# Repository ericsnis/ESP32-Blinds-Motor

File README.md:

# ESP32 Blinds Motor
Blind motor automation using MQTT & ESP32

## Features

  It connects to an MQTT server and:
  - checks washing blinds open/closed status (topic blinds/nbrblind1)
    - MQTT subscription can be changed to suit by changing TOPIC1
  - checks current open/closed flag
    - Ignores MQTT command if the flag and the MQTT status are the same
  - opens and closes blinds based on status
  - Polls the open and close blinds and calibration buttons
    - If calibration button is pressed it toggles calibration mode
      - Lights status LED to indicate in calibration mode
      - Open blinds button steps motor toward open 1/4 turn
      - Close blinds button steps motor toward closed 1/4 turn
    - If out of calibration mode
      - Open blinds button rotates motor toward full open
      - Close blinds button rotates motor toward full closed
    - Up & Down also updates the blind status in MQTT
    - Pin definitions
      - Calibration on pin 5
      - Up button on pin 39
      - Down button on pin 36
    Amount of backlash in the blinds rod can be adjusted

  Stepper driver info
  - Uses ULN2003 based board KS0327 Keyestudio stepper motor drive board
  - The stepper driver is attached to digital pins 9, 13, 12 & 14 of the ESP32.
    - Pins defined as Stepper1In1, Stepper1In2, Stepper1In3, etc.
    - Connect in the order they appear on board i.e. In1, In2, In3, In4
  - Driver board should be connected to 5V source

  Assumes use of ESP32 based NodeMCU board, not similarly named ESP8266 NodeMCU.
  - Can be changed to other boards if pinout is changed

  Uses the following libraries
  - Arduino stepper library released under GNU Lesser General Public
  - PubSubClient by Nick O'Leary released under MIT license

## Boards
The schematic folder contains the board and schematic files in Eagle format
- Designs use 1206 SMT LEDs and resistors
- One design excludes headers for endstop microswitches
- One design includes a header for a endstop microswitch

- ESP32 Blinds Motor

- ESP32 Blinds Motor w/ Endstop Header

## Code
The code folder contains the program code to compile and upload to the ESP32
- Use [Platform.io](https://docs.platformio.org/en/latest/integration/ide/vscode.html) installed on [Visual Studio Code](https://code.visualstudio.com/) AKA: VSCode to compile and upload.
- Open the code folder in VSCode then compile, PlatformIO should download any dependencies.
- Project Environments
  - esp32dev-steppermqtt no endstops - Firmware without endstops enabled
  - esp32dev-stepper mqtt with endstop - Firmware with endstops enabled
  - esp32dev-stepper test - Stepper motor connection test

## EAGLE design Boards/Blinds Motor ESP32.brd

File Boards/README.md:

# Boards
 The schematic folder contains the board and schematic files in Eagle format

## Files for ESP32 Blinds Motor w/o Endstop Headers
- _Blinds Motor ESP32.brd_ - Blinds Motor board file
- _Blinds Motor ESP32.sch_ - Blinds Motor schematic file

## Files for ESP32 Blinds Motor with Endstop Headers
- _Blinds Motor ESP32 w endstops.brd_ - Blinds Motor with Endstop board file
- _Blinds Motor ESP32 w endstops.sch_ - Blinds Motor with Endstop schematic file

**You need _both_ the .brd and .sch files to open the board in Eagle.**

## Designs
- One design excludes headers for endstop microswitches
- One design includes a header for a endstop microswitch
ESP32 Blinds Motor

ESP32 Blinds Motor w/ Endstop Header

**Files are provided as is with no guarantees express or implied**

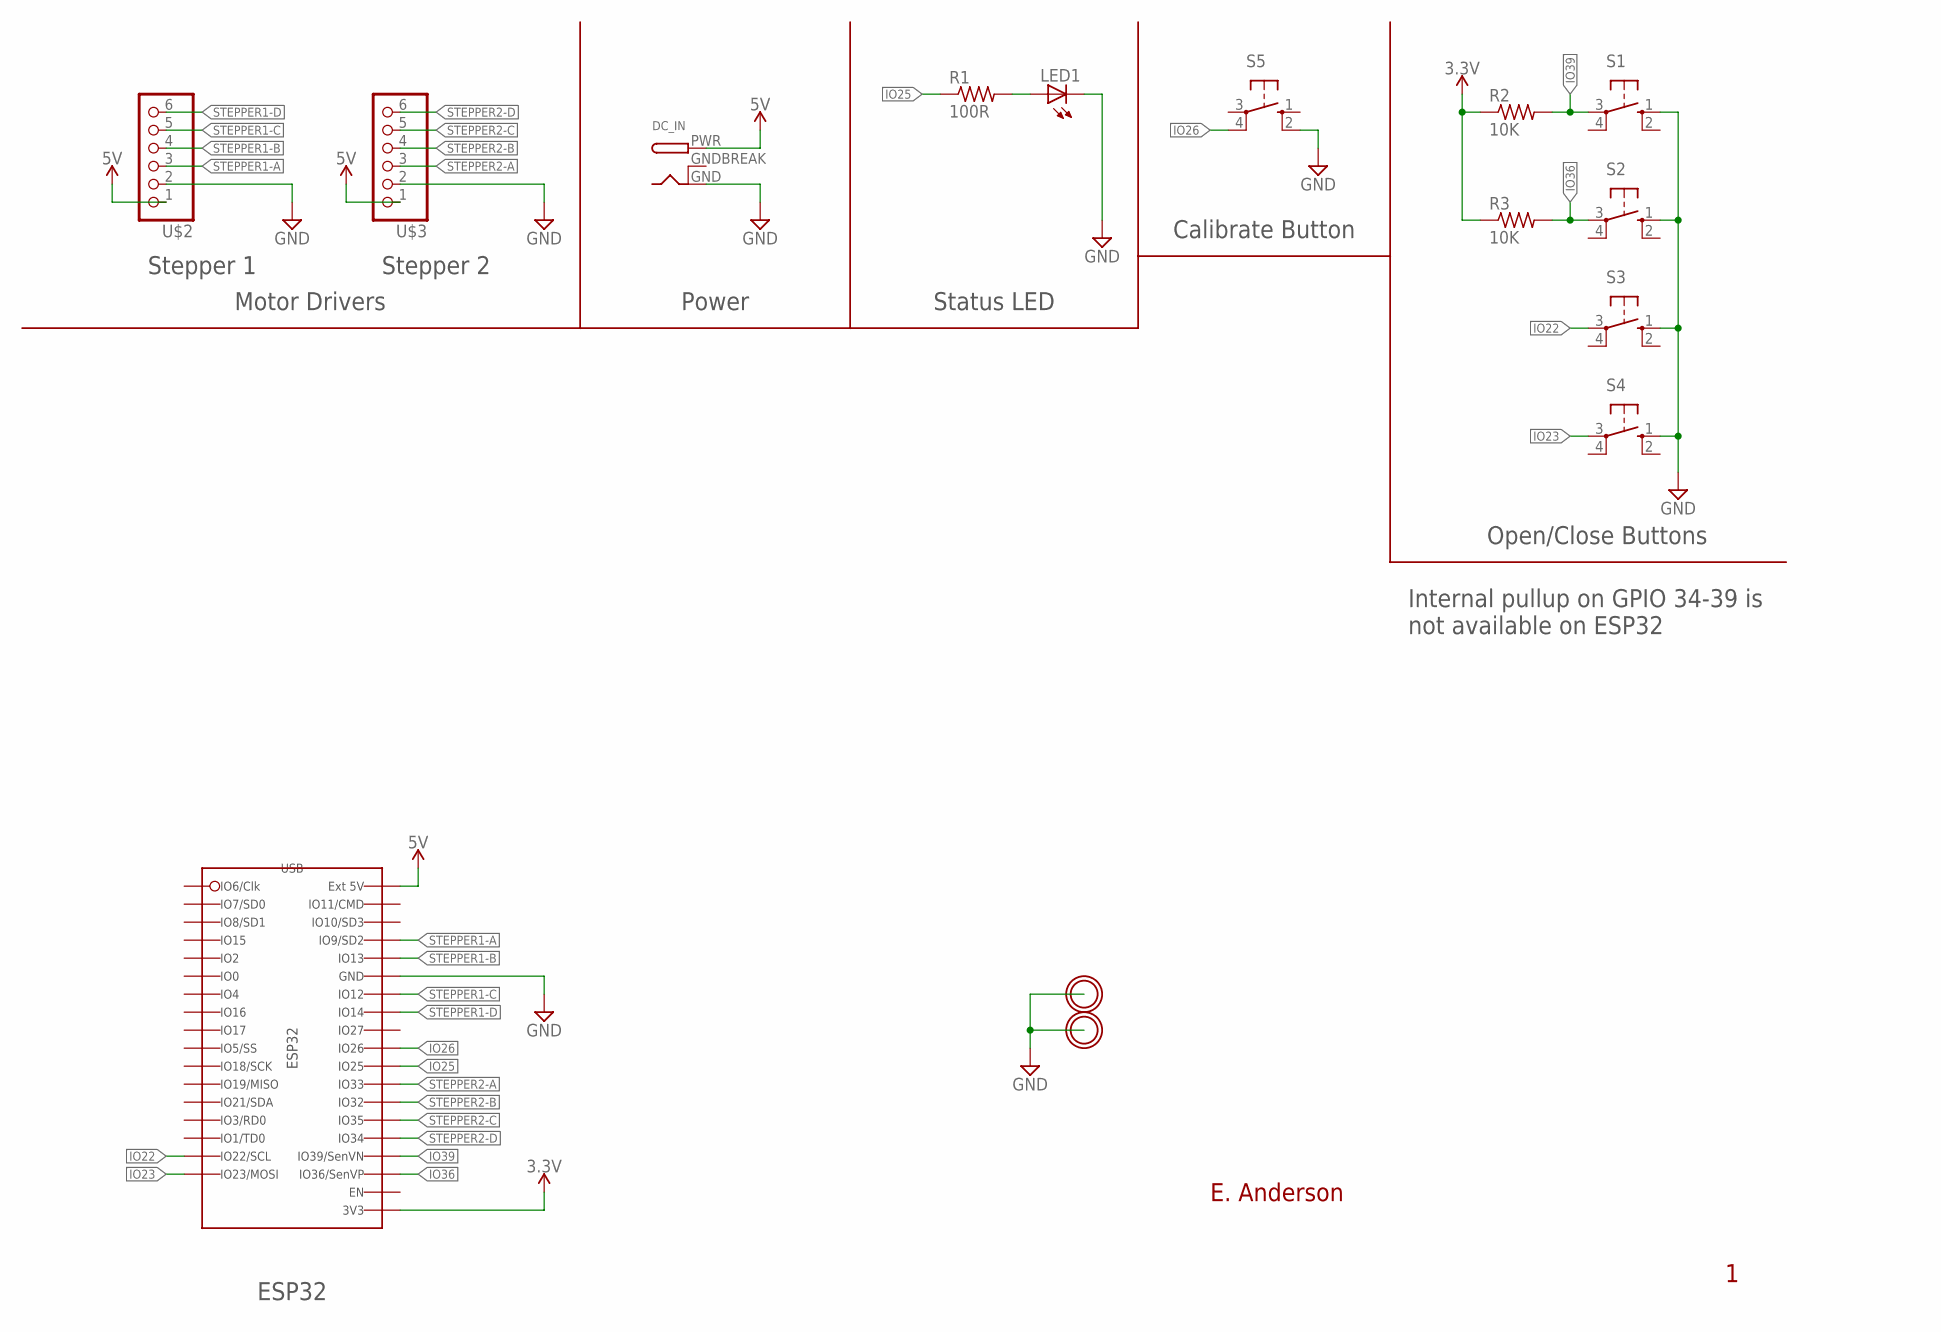
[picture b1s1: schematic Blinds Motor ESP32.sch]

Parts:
DC_IN: DCBARRELPTH; DCJACK_2MM_PTH
LED1: LED-CHIPLED_1206_LONG; CHIPLED_1206_LONG
R1: 100R; R1206
R2, R3: 10K; R1206
S1, S2, S3, S4, S5: B3F-10XX
U$2: Stepper 1; 1X06
U$3: Stepper 2; 1X06
U$5, U$6: MICROBUILDER_MOUNTINGHOLE3.0THIN; MICROBUILDER_MOUNTINGHOLE_3.0_PLATEDTHIN
U$7: ESP32-DEV; ESP32_DEV

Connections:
3.3V: R2.1, R3.1, U$7.3V3
5V: DC_IN.PWR, U$2.1, U$3.1, U$7.5V (EXT_5V)
GND: DC_IN.GND, LED1.C, S1.1 (S), S2.1 (S), S3.1 (S), S4.1 (S), S5.2 (S1), U$2.2, U$3.2, U$7.GND (GND1), U$7.GND1, U$7.GND2 (GND1)
GNDBREAK: DC_IN.GNDBREAK
IO22: S3.3, U$7.IO22
IO23: S4.3, U$7.IO23 (IO23/SCL)
IO25: R1.1, U$7.IO25
IO26: S5.4 (P1), U$7.IO26
IO36: R3.2, S2.3, U$7.IO36-SVP (IO36/SVP)
IO39: R2.2, S1.3, U$7.IO39-SVN (IO39/SVN)
unnamed: LED1.A, R1.2
STEPPER1-A: U$2.3, U$7.IO9-SD2 (IO9/SD2)
STEPPER1-B: U$2.4, U$7.IO13
STEPPER1-C: U$2.5, U$7.IO12
STEPPER1-D: U$2.6, U$7.IO14
STEPPER2-A: U$3.3, U$7.IO33
STEPPER2-B: U$3.4, U$7.IO32
STEPPER2-C: U$3.5, U$7.IO35
STEPPER2-D: U$3.6, U$7.IO34

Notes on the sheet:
Stepper 1
Stepper 2
ESP32
Power
Open/Close Buttons
Motor Drivers
Calibrate Button
Status LED
Internal pullup on GPIO 34-39 is not available on ESP32

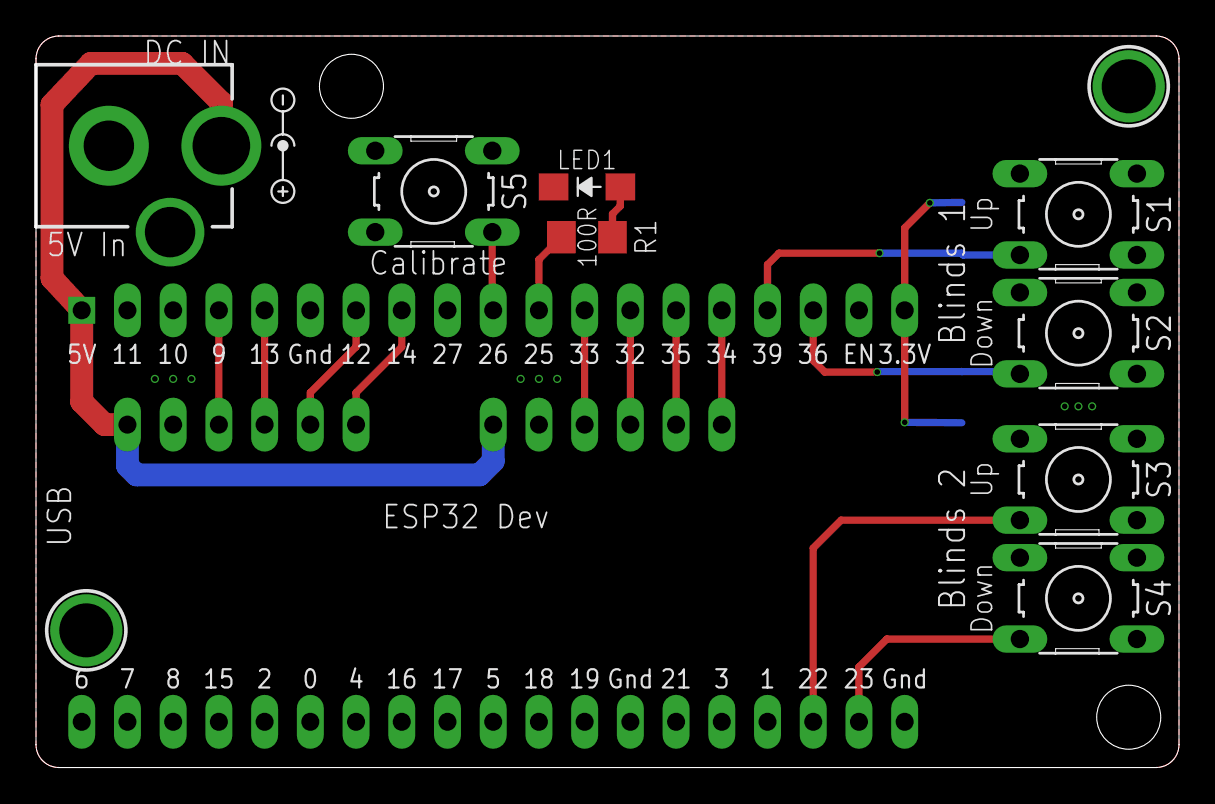
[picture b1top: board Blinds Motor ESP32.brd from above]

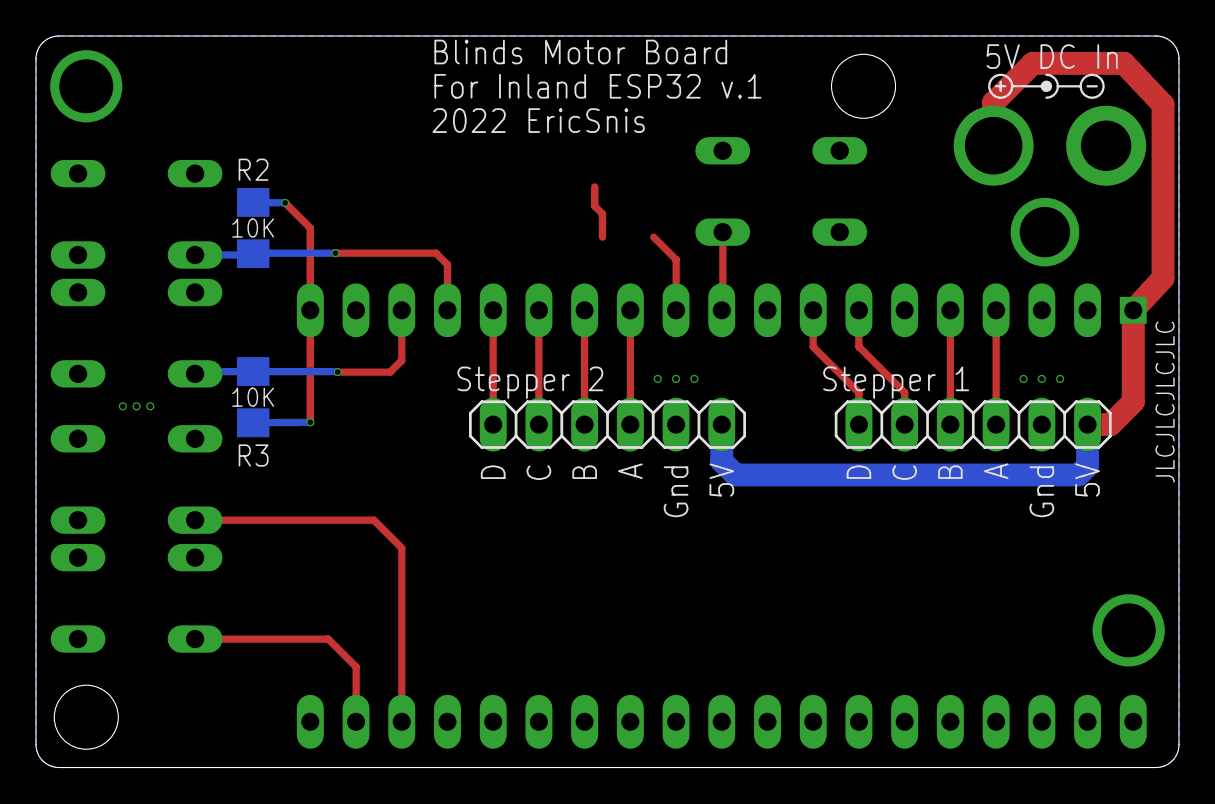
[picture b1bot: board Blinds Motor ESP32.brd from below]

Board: 2 copper layers, 63.5 x 40.6 mm, 17 parts (5 on the bottom side), 18 nets.

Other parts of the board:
U$4, U$8: CENTER-POS-SMALL

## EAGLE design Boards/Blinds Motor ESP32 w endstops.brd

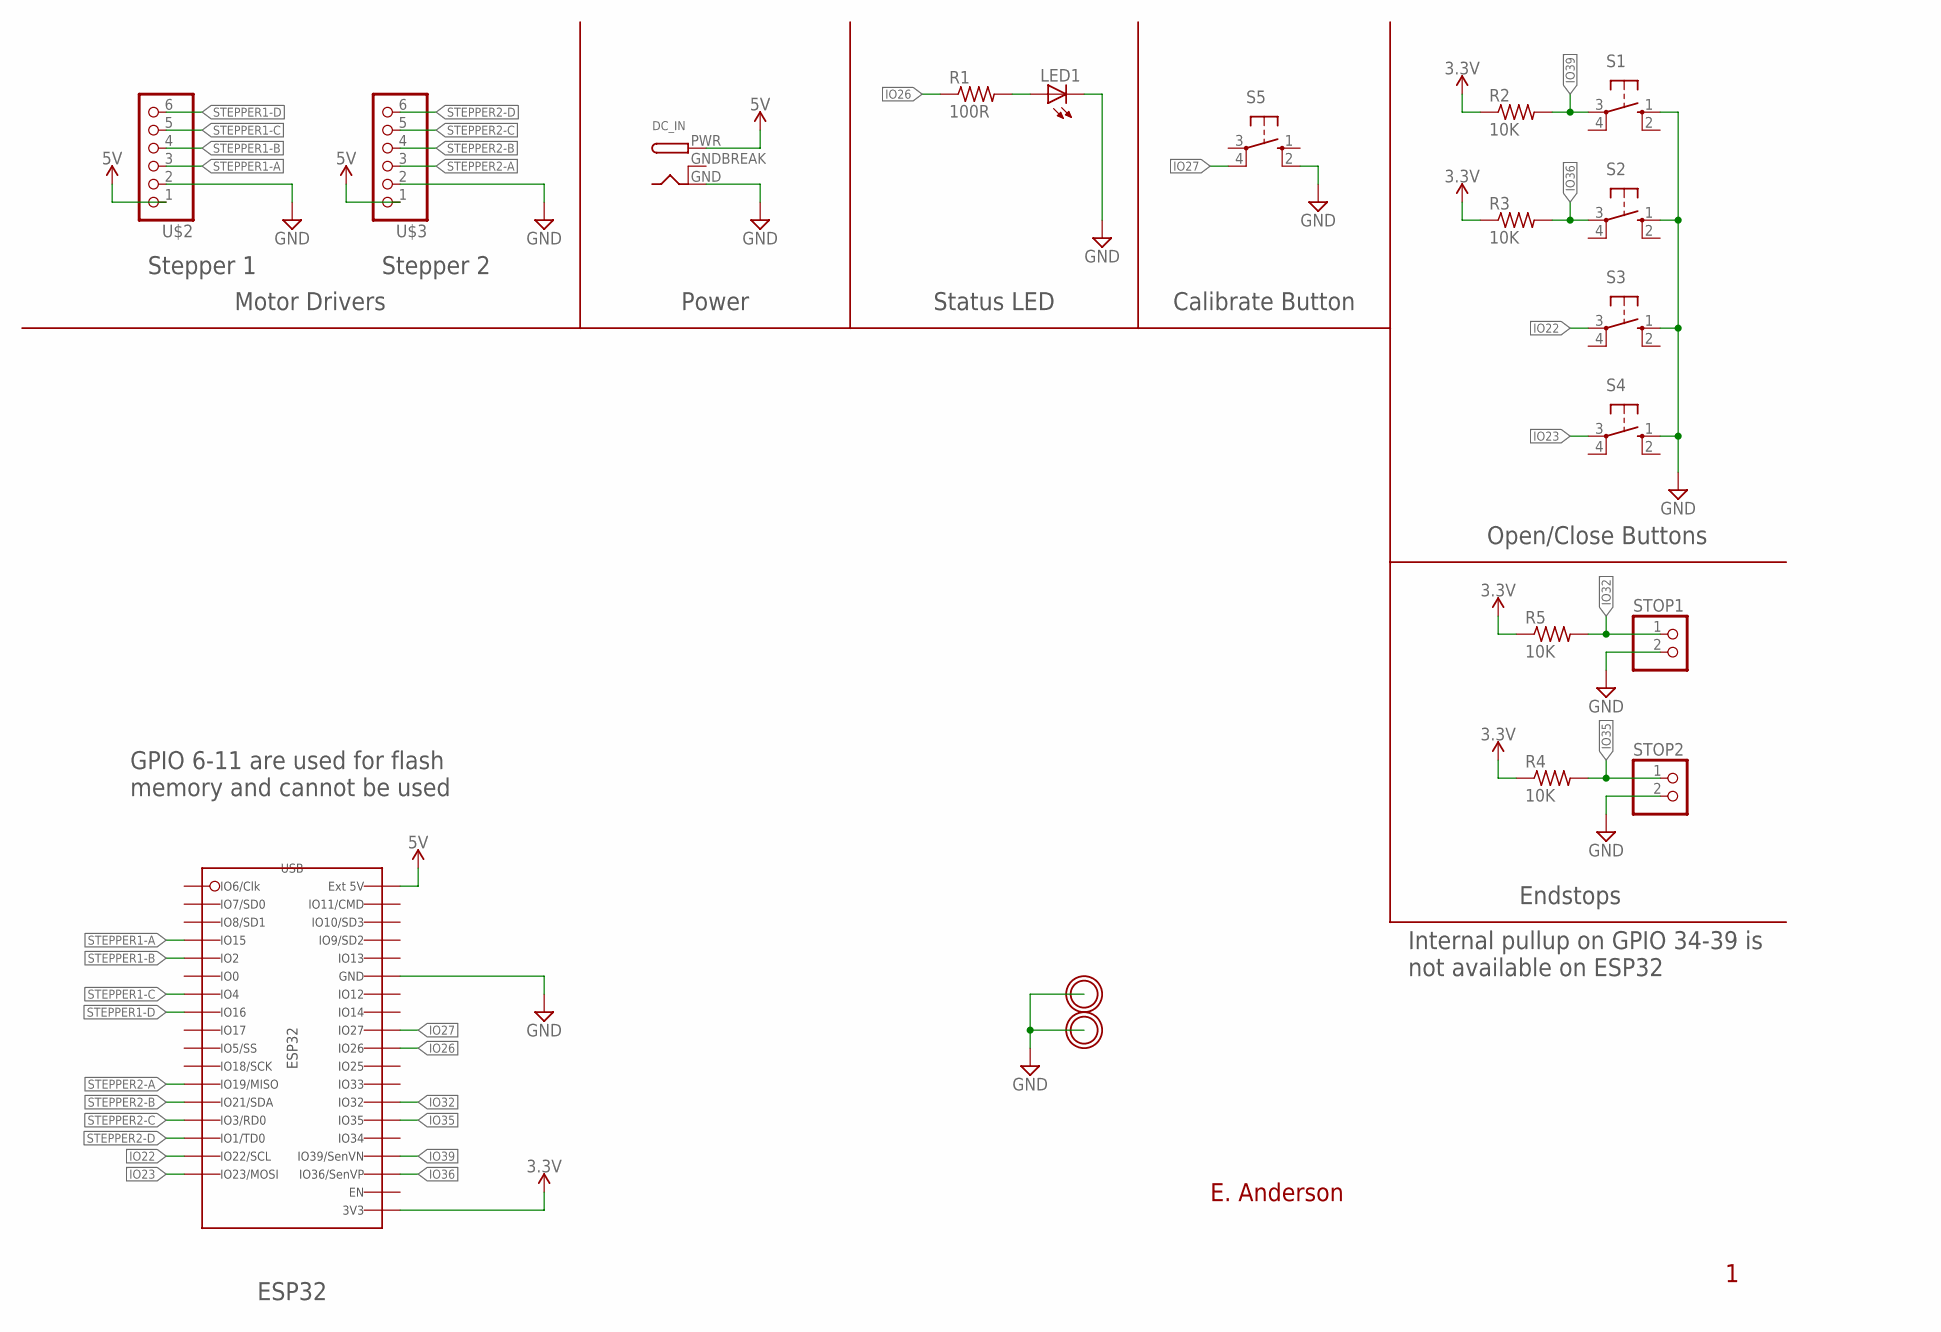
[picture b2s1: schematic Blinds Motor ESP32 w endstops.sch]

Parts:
DC_IN: DCBARRELPTH; DCJACK_2MM_PTH
LED1: LED-CHIPLED_1206_LONG; CHIPLED_1206_LONG
R1: 100R; R1206
R2, R3, R4, R5: 10K; R1206
S1, S2, S3, S4, S5: B3F-10XX
STOP1, STOP2: 1X2_HEADER_LONG; 1X02
U$2: Stepper 1; 1X06
U$3: Stepper 2; 1X06
U$5, U$6: MICROBUILDER_MOUNTINGHOLE3.0THIN; MICROBUILDER_MOUNTINGHOLE_3.0_PLATEDTHIN
U$7: ESP32-DEV; ESP32_DEV

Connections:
3.3V: R2.1, R3.1, R4.1, R5.1, U$7.3V3
5V: DC_IN.PWR, U$2.1, U$3.1, U$7.5V (EXT_5V)
GND: DC_IN.GND, LED1.C, S1.1 (S), S2.1 (S), S3.1 (S), S4.1 (S), S5.2 (S1), STOP1.2, STOP2.2, U$2.2, U$3.2, U$7.GND (GND1), U$7.GND1, U$7.GND2 (GND1)
GNDBREAK: DC_IN.GNDBREAK
IO22: S3.3, U$7.IO22
IO23: S4.3, U$7.IO23 (IO23/SCL)
IO26: R1.1, U$7.IO26
IO27: S5.4 (P1), U$7.IO27
IO32: R5.2, STOP1.1, U$7.IO32
IO35: R4.2, STOP2.1, U$7.IO35
IO36: R3.2, S2.3, U$7.IO36-SVP (IO36/SVP)
IO39: R2.2, S1.3, U$7.IO39-SVN (IO39/SVN)
unnamed: LED1.A, R1.2
STEPPER1-A: U$2.3, U$7.IO15
STEPPER1-B: U$2.4, U$7.IO2
STEPPER1-C: U$2.5, U$7.IO4
STEPPER1-D: U$2.6, U$7.IO16
STEPPER2-A: U$3.3, U$7.IO19
STEPPER2-B: U$3.4, U$7.IO21 (IO21/SDA)
STEPPER2-C: U$3.5, U$7.IO3-RXD0 (RXD0)
STEPPER2-D: U$3.6, U$7.IO1-TXD0 (TXD0)

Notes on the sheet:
Stepper 1
Stepper 2
ESP32
Power
Open/Close Buttons
Motor Drivers
Calibrate Button
Status LED
Internal pullup on GPIO 34-39 is not available on ESP32
Endstops
GPIO 6-11 are used for flash memory and cannot be used

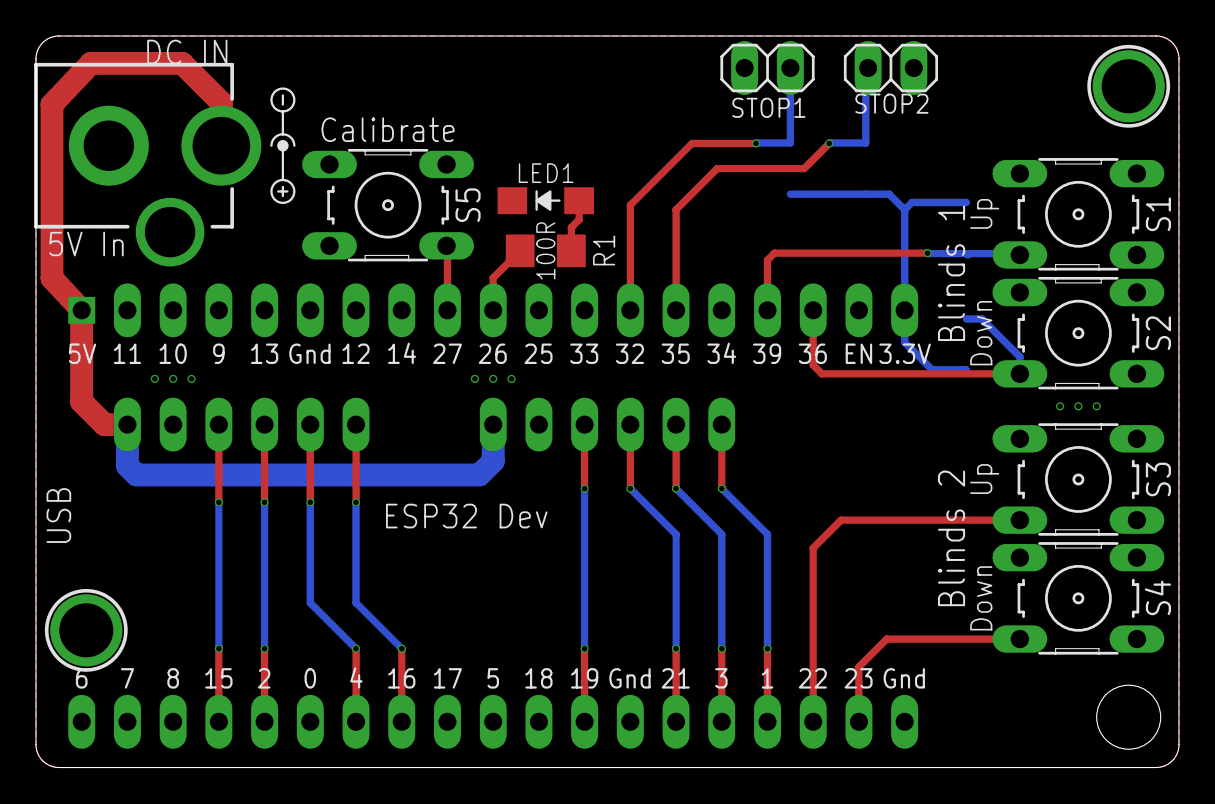
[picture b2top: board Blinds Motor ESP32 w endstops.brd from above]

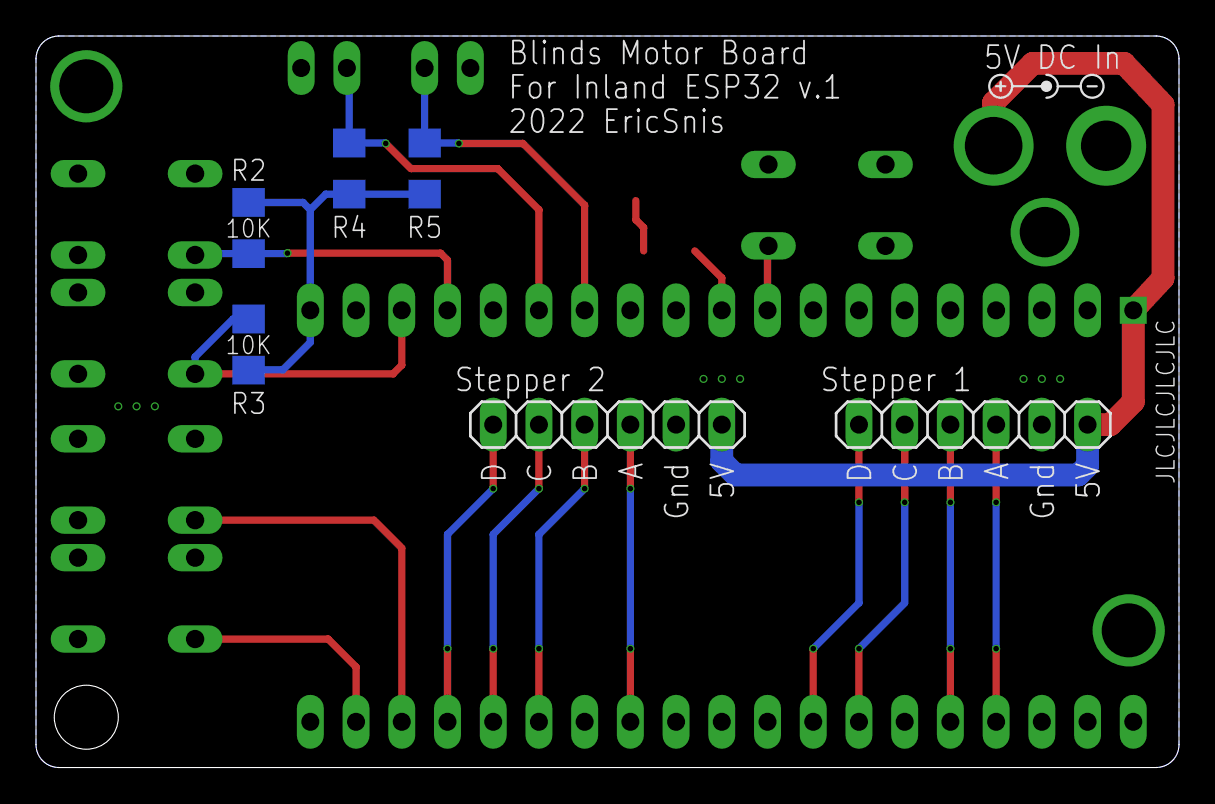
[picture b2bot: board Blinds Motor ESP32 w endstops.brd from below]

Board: 2 copper layers, 63.5 x 40.6 mm, 21 parts (7 on the bottom side), 20 nets.

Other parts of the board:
U$4, U$8: CENTER-POS-SMALL
